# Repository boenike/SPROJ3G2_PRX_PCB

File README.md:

# SPROJ3G2_PRX_PCB
SPROJ3EEG2 PRX PCB - KiCad files

Author: Bence Tóth

Course: BEng in Electronics

Campus: SDU Sonderborg

Semester: 3rd

Finish date: 2024/12/23

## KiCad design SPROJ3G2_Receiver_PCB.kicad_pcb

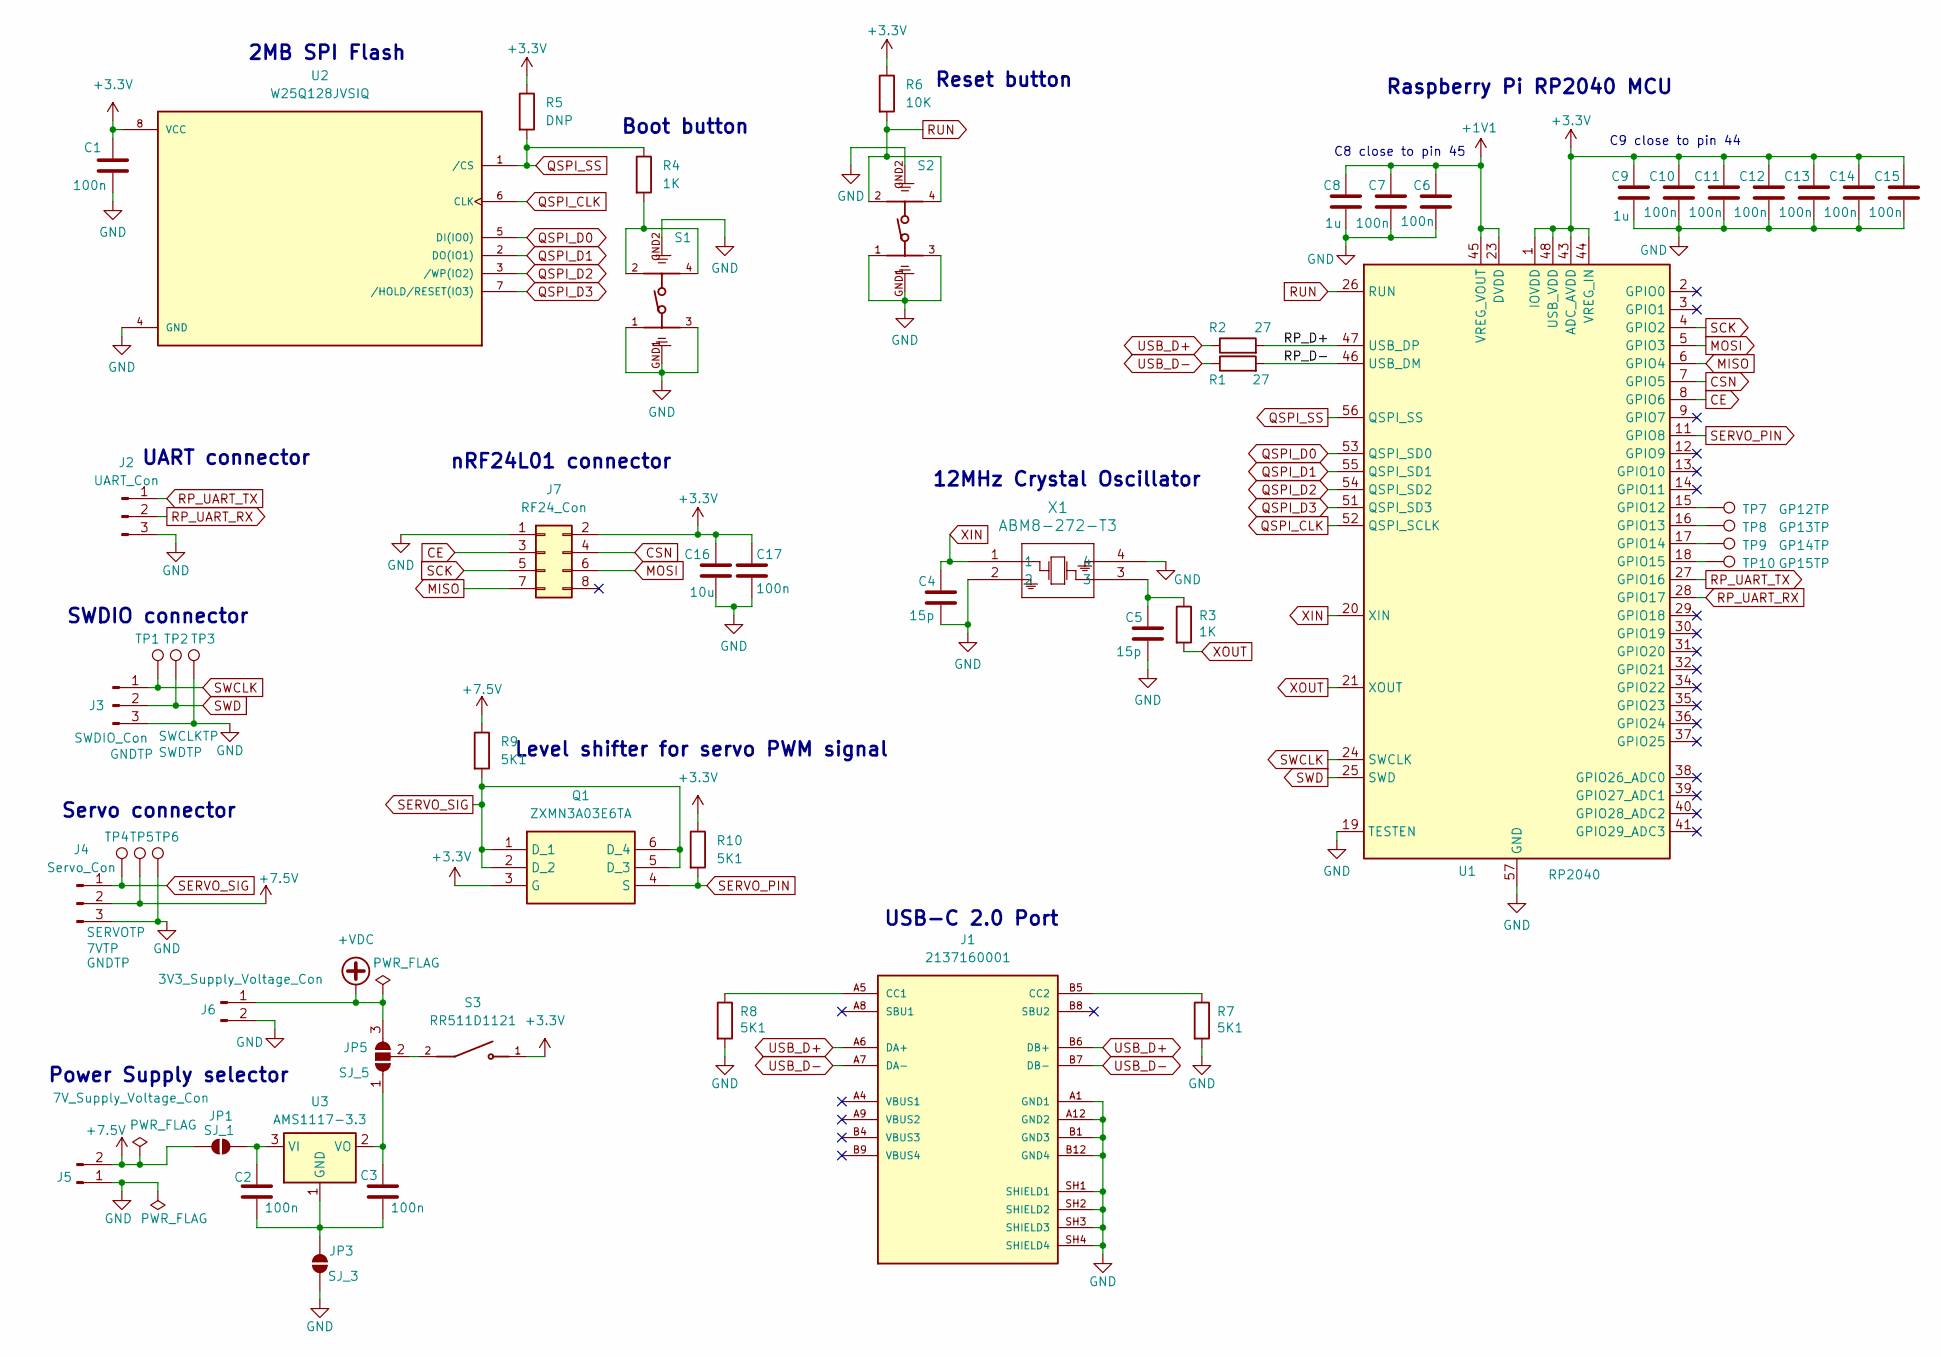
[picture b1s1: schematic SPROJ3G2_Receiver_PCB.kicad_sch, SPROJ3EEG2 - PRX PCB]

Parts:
C1, C2, C3, C6, C7, C10, C11, C12, C13, C14, C15, C17: 100n; C_0805_2012Metric
C4, C5: 15p; C_0805_2012Metric
C8, C9: 1u; C_0805_2012Metric
C16: 10u; C_0805_2012Metric
J1: 2137160001; PARTREV B
J2: UART_Con; JST_PH_S3B-PH-K_1x03_P2.00mm_Horizontal
J3: SWDIO_Con; JST_PH_S3B-PH-K_1x03_P2.00mm_Horizontal
J4: Servo_Con; PinHeader_1x03_P2.54mm_Horizontal
J5: 7V_Supply_Voltage_Con; JST_PH_S2B-PH-K_1x02_P2.00mm_Horizontal
J6: 3V3_Supply_Voltage_Con; JST_PH_S2B-PH-K_1x02_P2.00mm_Horizontal
J7: RF24_Con; PinHeader_2x04_P2.54mm_Vertical
JP1: SJ_1; SolderJumper-2_P1.3mm_Open_RoundedPad1.0x1.5mm
JP3: SJ_3; SolderJumper-2_P1.3mm_Open_RoundedPad1.0x1.5mm
JP5: SJ_5; SolderJumper-3_P1.3mm_Open_RoundedPad1.0x1.5mm_NumberLabels
Q1: ZXMN3A03E6TA; Manufacturer_Part_Number ZXMN3A03E6TA; Mouser Part Number 522-ZXMN3A03E6TA
R1, R2: 27; R_0805_2012Metric
R3, R4: 1K; R_0805_2012Metric
R5: DNP; R_0805_2012Metric
R6: 10K; R_0805_2012Metric
R7, R8, R9, R10: 5K1; R_0805_2012Metric
S1, S2: 431183015816; PART-NUMBER 431183015816
S3: RR511D1121; PARTREV A
TP1: SWCLKTP; TestPoint_Pad_D1.0mm
TP2: SWDTP; TestPoint_Pad_D1.0mm
TP3, TP6: GNDTP; TestPoint_Pad_D1.0mm
TP4: SERVOTP; TestPoint_Pad_D1.0mm
TP5: 7VTP; TestPoint_Pad_D1.0mm
TP7: GP12TP; TestPoint_Pad_D1.0mm
TP8: GP13TP; TestPoint_Pad_D1.0mm
TP9: GP14TP; TestPoint_Pad_D1.0mm
TP10: GP15TP; TestPoint_Pad_D1.0mm
U1: RP2040; QFN-56-1EP_7x7mm_P0.4mm_EP3.2x3.2mm
U2: W25Q128JVSIQ; PARTREV I
U3: AMS1117-3.3; SOT-223-3_TabPin2
X1: ABM8-272-T3; ABM8-272-T3_ABR

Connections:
+1V1: C6.1, C7.1, C8.1, U1.23 (DVDD), U1.45 (VREG_VOUT), U1.50 (DVDD)
+3.3V: C1.1, C9.1, C10.1, C11.1, C12.1, C13.1, C14.1, C15.1, C16.1, C17.1, J7.2, Q1.3 (G), R5.1, R6.1, R10.1, S3.1, U1.1 (IOVDD), U1.10 (IOVDD), U1.22 (IOVDD), U1.33 (IOVDD), U1.42 (IOVDD), U1.43 (ADC_AVDD), U1.44 (VREG_IN), U1.48 (USB_VDD), U1.49 (IOVDD), U2.8 (VCC)
+7.5V: J4.2, J5.2, JP1.1 (A), R9.1, TP5.1
+VDC: J6.1, JP5.3 (B)
/RP_D+: R2.2, U1.47 (USB_DP)
/RP_D-: R1.2, U1.46 (USB_DM)
CE: J7.3, U1.8 (GPIO6)
CSN: J7.4, U1.7 (GPIO5)
GND: C1.2, C4.2, C5.2, C6.2, C7.2, C8.2, C9.2, C10.2, C11.2, C12.2, C13.2, C14.2, C15.2, C16.2, C17.2, J1.A1 (GND1), J1.A12 (GND2), J1.B1 (GND3), J1.B12 (GND4), J1.SH1 (SHIELD1), J1.SH2 (SHIELD2), J1.SH3 (SHIELD3), J1.SH4 (SHIELD4), J2.3, J3.3, J4.3, J5.1, J6.2, J7.1, JP3.2 (B), R7.2, R8.2, S1.1, S1.3, S1.GND1, S1.GND2, S2.1, S2.3, S2.GND1, S2.GND2, TP3.1, TP6.1, U1.19 (TESTEN), U1.57 (GND), U2.4 (GND), X1.2, X1.4
MISO: J7.7, U1.6 (GPIO4)
MOSI: J7.6, U1.5 (GPIO3)
unnamed: C5.1, R3.1, X1.3
unnamed: J1.A5 (CC1), R8.1
unnamed: J1.B5 (CC2), R7.1
unnamed: C2.1, JP1.2 (B), U3.3 (VI)
unnamed: C2.2, C3.2, JP3.1 (A), U3.1 (GND)
unnamed: C3.1, JP5.1 (A), U3.2 (VO)
unnamed: JP5.2 (C), S3.2
unnamed: R4.2, S1.2, S1.4
unnamed: TP7.1, U1.15 (GPIO12)
unnamed: TP8.1, U1.16 (GPIO13)
unnamed: TP9.1, U1.17 (GPIO14)
unnamed: TP10.1, U1.18 (GPIO15)
QSPI_CLK: U1.52 (QSPI_SCLK), U2.6 (CLK)
QSPI_D0: U1.53 (QSPI_SD0), U2.5 (DI(IO0))
QSPI_D1: U1.55 (QSPI_SD1), U2.2 (DO(IO1))
QSPI_D2: U1.54 (QSPI_SD2), U2.3 (/WP(IO2))
QSPI_D3: U1.51 (QSPI_SD3), U2.7 (/HOLD/RESET(IO3))
QSPI_SS: R4.1, R5.2, U1.56 (QSPI_SS), U2.1 (/CS)
RP_UART_RX: J2.2, U1.28 (GPIO17)
RP_UART_TX: J2.1, U1.27 (GPIO16)
RUN: R6.2, S2.2, S2.4, U1.26 (RUN)
SCK: J7.5, U1.4 (GPIO2)
SERVO_PIN: Q1.4 (S), R10.2, U1.11 (GPIO8)
SERVO_SIG: J4.1, Q1.1 (D_1), Q1.2 (D_2), Q1.5 (D_3), Q1.6 (D_4), R9.2, TP4.1
SWCLK: J3.1, TP1.1, U1.24 (SWCLK)
SWD: J3.2, TP2.1, U1.25 (SWD)
USB_D+: J1.A6 (DA+), J1.B6 (DB+), R2.1
USB_D-: J1.A7 (DA-), J1.B7 (DB-), R1.1
XIN: C4.1, U1.20 (XIN), X1.1
XOUT: R3.2, U1.21 (XOUT)

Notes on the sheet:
Boot button
Level shifter for servo PWM signal
C8 close to pin 45
USB-C 2.0 Port
SWDIO connector
Raspberry Pi RP2040 MCU
nRF24L01 connector
2MB SPI Flash
Reset button
C9 close to pin 44
Power Supply selector
Servo connector
12MHz Crystal Oscillator
UART connector

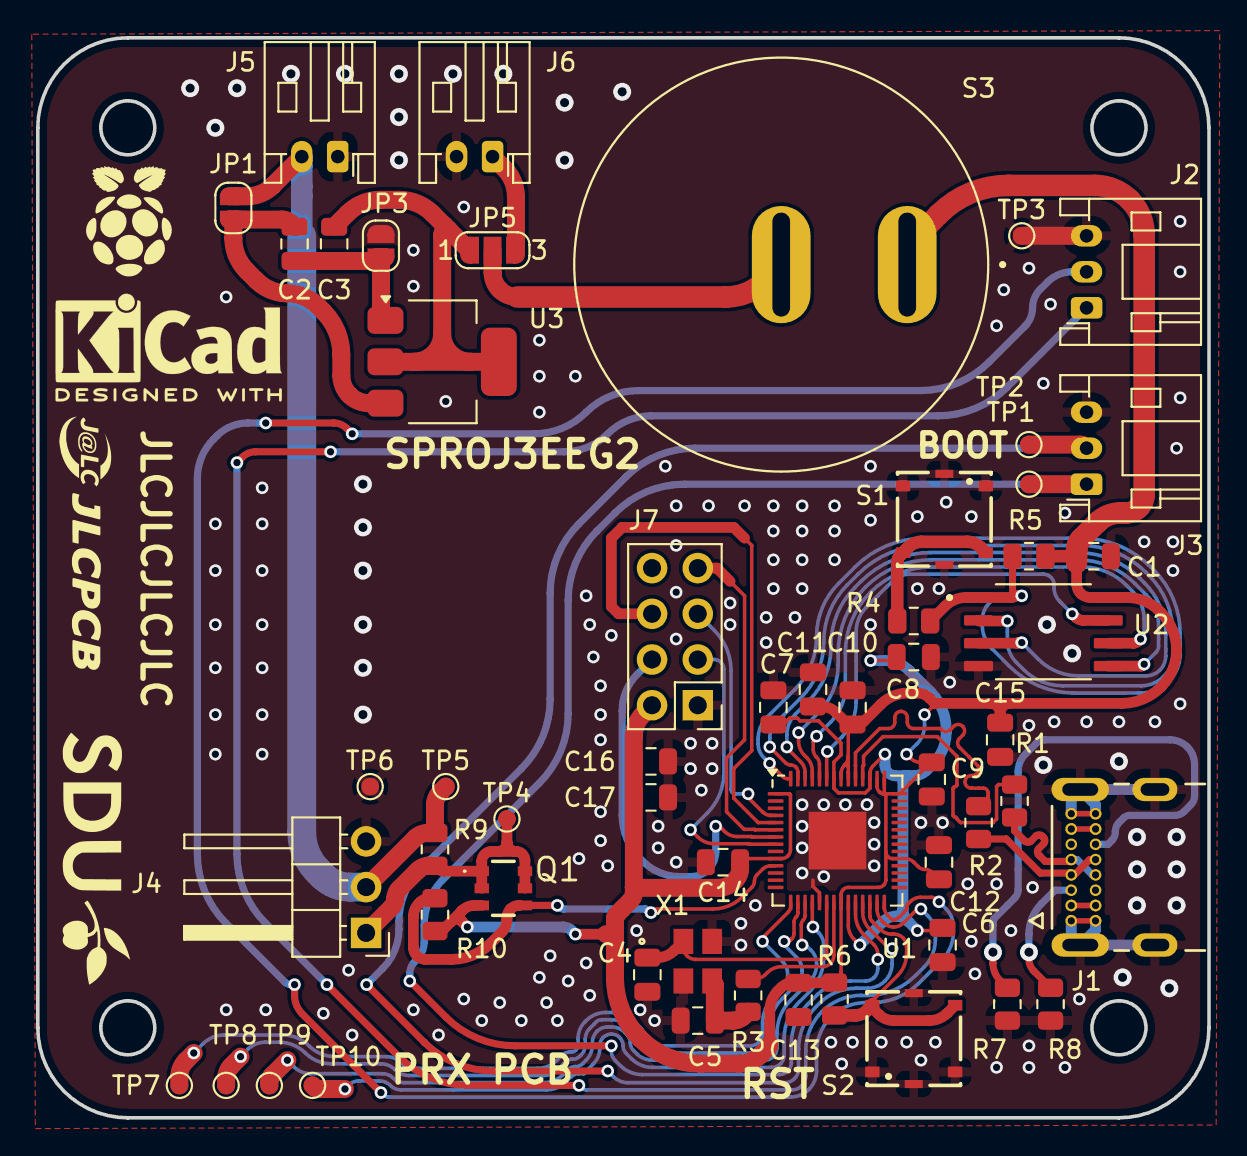
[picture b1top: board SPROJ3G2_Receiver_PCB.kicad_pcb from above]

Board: 2 copper layers, 65.1 x 60.0 mm, 55 parts (0 on the bottom side), 41 nets.

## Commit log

2024-12-09 PCB files upload
    PCB files upload
2024-12-20 Schematic cleanup
    Schematic cleanup
2024-12-20 Clean-up
    Clean-up
